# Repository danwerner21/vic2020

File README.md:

# Vic-2020
A Vic-20 clone created with [almost] all readily available parts

## Introduction
This project is an implementation of a VIC-20 (mostly) compatible computer. The project is built using a combination of 1980's era components (7400-series logic) and more modern components- such as a modern 6502 variant and 512 KiB SRAM and 512 KiB Flash ROMs. The only hard to find component is the MOS 6560 VIC video chip -- and it is my hope to follow up this project with a project to replace that chip with a FPGA replacement, providing the open source community a full path to re-creating the VIC-20 with all new components.

## Why?
Why would I do a replica of the VIC-20?   Well, like many others the VIC-20 was my first computer.  In 1981 I spent most of my (non-school) waking hours learning everything possible about this machine, and that launched me into a successful career in IT.   In the early 2000s I discovered the retro-computer scene and have spent many hours building and creating new retro computer designs following the work happening in such places as 6502.org and retrobrewcomputers.org.  So much so, that my boss has taken to giving me crap about spending my free time "Building VIC-20s" . . . .   It was earlier in 2020 when he had made one such comment that I realized that while I had constructed many vintage designs, I had never actually built a VIC-20.  I decided that I should correct that oversight as soon as possible -- and thus the VIC-2020 Fichter Edition (named after my boss) was born.

---

## What is included in this repo?
As of this time, the repo includes

1. The VIC-2020 Mainboard PCB Kicad design and Gerber files
2. The VIC-2020 Keyboard PCB Kicad design and Gerber files
3. OpenSCAD and STL files for a 3d printed case
4. Design Files for Max Keyboard Custom Printed Keycaps

---

## Known Bugs

* While the mainboard does have a S-VIDEO mod applied that should (in theory) provide S-VIDEO output, it does not work.   If anyone corrects this, please feel free to reach out and I will correct the schematics -- but for now, I would not populate the S-VIDEO connector, and always short the Chroma Disconnect jumper.
#### UPDATE
 Turns out the footprint for the SVIDEO connector in KiCad has the pins numbered incorrectly and that is the cause of the SVIDEO issue.   I have updated the PCB and Schematic to account for this, but have not tested the fix myself.  I am told that the SVIDEO out does work with a properly wired cable.

 note that the 1.1 version of the PCB still have the Chroma/Luma pins reversed on the video connector.  Seems that I made a patch to correct the pins and KiCAD also made a patch to correct the PCB layout of the connector, and thus reversed each other's work. . .  1.2 should be correct, but as always until it is tested, assume it needs patched.

---

## How is the VIC-2020 the same as a VIC-20?

The VIC-2020 should be mostly software compatible with the expanded and unexpanded Commodore VIC-20.   I have tested a variety of cartridges (commodore and third party) and have ran several homebrew and commercial disk based programs on the system with no issues.   Note that this does use a more modern variant of the 6502, so software relying on 6502 undocumented opcodes or bugs will not work properly.  The VIC-2020 has a commodore compatible IEC port that has been tested with a real 1571 and real 1541 and seems to work properly with one exception -- if the device holds the RESET line low the system will not function.   This can be observed if the VIC-2020 is connected to a powered off IED device -- the VIC will not function until the IEC device is powered on or unplugged from the VIC.

---

## How is the VIC-2020 different from a VIC-20?

Because the VIC-2020 is using more modern parts, it has ALOT of ram compared to the VIC-20.   The original VIC-20 shipped with 4k of ram . . .  the VIC-2020 has 256k.  This has some implications.   First, for compatibility there is a portion of the RAM that is just wasted. Of the 128k chip that is used for main memory, only 32k is accessible, the rest is hidden.  This is a design trade off that made the system less complex and ensured compatibility.   That said, small design changes were made to allow the 128k color ram to be totally usable by the system.  The first modification allowed all 8 bits of color ram to be used as storage for the system.  In the original VIC-20, color ram was only 4 bits wide, as the VIC chip only needs 4 bits to store color information.  In the VIC-2020 design all 8 bits are available to the CPU, even though only 4 bits are used by the VIC chip.  This should allow a programmer to store user information in the upper 4 bits of the color ram without affecting any other part of the system.   Also, the 6522 IO port that was dedicated to the user port on the VIC-20 has been repurposed as a "Page Register" (located at 0x9110 or 37136) on the VIC-2020 allowing 128 pages of color ram to be available for the VIC chip.  This should give the ability for some very interesting color effects to be produced on the VIC-2020, while still keeping the VIC mostly compatible.  This technique was demonstrated as early as 2010 in the sleepingelephant.com forums [here](http://sleepingelephant.com/ipw-web/bulletin/bb/viewtopic.php?t=4882).

### Power
Unlike the original, the VIC-2020 will run off of one regulated 5V 1.5A power supply.

### Ports
In order to simplify the VIC-2020s power requirements, the cassette and user ports were ommitted from the system.   It is possible to use the lines in the AUX connector (J11) and the IEC port to gain access to the cassette data lines if one wanted to use a cassette emulator.  The cartridge port is mostly compatible (assuming proper setting of SW3) with the omission of the RAM1,RAM2, & RAM3 lines.
Note that trimmer RV1 can be used to adjust video signal output strength.  If your particular TV appears either overdriven or too dim, adjust RV1 accordingly.   Variable Cap C2 can be used to adjust video signal phase -- adjust this trimmer if your VIC shows no color or the wrong colors.

### Ram Configuration
For simplicity sake, the VIC-2020 in even its lowest memory configuration has the VIC 3K memory expansion enabled at RAM1, RAM2, and RAM3, giving it 8K of base ram, 6.5k free for BASIC.   This configuration is totally compatible with most "unexpanded" VIC software, but is incompatible with any cartridge that includes the 3k RAM expansion option (such as the VIC Super Expander Cartridge).  The other RAM configuration options for BLK1, BLK2, BLK3, and BLK5 are DIP switch selectable allowing memory to be configured.   It is best to have each RAM block only assigned to either the Expansion Port (SW3) or the Internal RAM (SW1) but not both at the same time.  When in doubt set all of SW3 to "on" and all of SW1 to "off" and you should have a mostly compatible unexpanded VIC.  For a mostly compatible expanded VIC set BLK1,BLK2, BLK3 on SW1 to "on" and SW3 to "off".

### Character ROM Configuration
The 8K 2764 EPROM at U19 contains the character ROM image for the VIC-2020.  The VIC chip only needs 4K to store a complete set of character images, so jumper J3 is used to select one of two character sets that can be stored on the 2764.  If pins 1&2 are shorted on the jumper the first 4K of the chip is used (addresses 0x0000-0x0FFF) for the character patterns and if pins 2&3 are shorted the second 4K (addresses 0x1000-0x1FFF) are used.

### System ROM Configuration
On the VIC-2020 it is possible to use several different types of main ROM chips and have several ROM images burned at the same time -- all selected by jumpers J1 and J2.

Jumper Settings|Chip Used|Resulting eprom configuration
---------------|---------|-----------------------
J1 1&2, J2 1&2|27512         | BASIC image at 0x0000 through 0x1FFF KERNAL at 0x2000 through 0x3FFF
J1 1&2, J2 1&2|27256         | BASIC image at 0x0000 through 0x1FFF KERNAL at 0x2000 through 0x3FFF
J1 1&2, J2 1&2|27128         | BASIC image at 0x0000 through 0x1FFF KERNAL at 0x2000 through 0x3FFF
J1 1&2, J2 2&3|27512         | BASIC image at 0x4000 through 0x5FFF KERNAL at 0x6000 through 0x7FFF
J1 1&2, J2 2&3|27256         | BASIC image at 0x4000 through 0x5FFF KERNAL at 0x6000 through 0x7FFF
J1 1&2, J2 2&3|27128         | NOT VALID
J1 2&3, J2 1&2|27512         | BASIC image at 0x8000 through 0x9FFF KERNAL at 0xA000 through 0xBFFF
J1 2&3, J2 1&2|27256         | NOT VALID
J1 2&3, J2 1&2|27128         | NOT VALID
J1 2&3, J2 1&2|27512         | BASIC image at 0xC000 through 0xDFFF KERNAL at 0xE000 through 0xFFFF
J1 2&3, J2 1&2|27256         | NOT VALID
J1 2&3, J2 1&2|27128         | NOT VALID

---

## Bill Of Materials

### Mainboard

Part Number|Quantity|Name
-----------|--------|----
C35,C36	|2|	.001uf Capacitor
C7,C12-C34|	23|	.01uf Capacitor
C1,C6,C8,C10,C40|	5|	.1uf Capacitor
C37	|1|	.47uF Electrolytic Capacitor
C38	|1|	10uF Electrolytic Capacitor
C4	|1|	10uf Capacitor
C11	|1|	1uf Electrolytic Capacitor
C9	|1|	2.2uF Electrolytic Capacitor
C5	|1|	220pf Capacitor
C3	|1|	2pf Capacitor
C39	|1|	47uF Capacitor
C2	|1|	8-90pf  Variable Capacitor
FB1-FB9|	9|	Ferrite_Bead_Small
J1,J2,J3|	3|	Pin Header 1x03 2.54mm
J10	|1|	Barrel Jack
J11	|1|	Pin Header 2x8 2.54mm
J12	|1|	Card Edge Connector 2x22 (Mouser #:587-305-044-520-502)
J13	|1|	DIN 6 IEC connector (mouser#571-9-211509)
J14	|1|	DSUB 9 Male
J4,J9	|2|	Pin Header 1x2 2.54mm
J5	|1|	DIN-4 (mouser#571-5749181-1)
J6,J7	|2|	RCA Jack
J8	|1|	Pin Header 1x20
Q1	|1|	2sc1959
Q2	|1|	2SC1815
R36	|1|	75ohm Resistor 1/4w
R15	|1|	180ohm Resistor 1/4w
R16	|1|	240ohm Resistor 1/4w
R22	|1|	270ohm Resistor 1/4w
R2,R4,R24	|3|	330ohm Resistor 1/4w
R21	|1|	470ohm Resistor 1/4w
R17	|1|	510ohm Resistor 1/4w
R3,R5	|2|	560ohm Resistor 1/4w
R19	|1|	1.8Kohm Resistor 1/4w
R23	|1|	10Kohm Resistor 1/4w
R6	|1|	150Kohm Resistor 1/4w
R7,R11-R14,R18,R25-R35	|16|	1K ohm Resistor 1/4w
R8-R10	|3|	2.2Kohm Resistor 1/4w
R20	|1|	2.7Kohm Resistor 1/4w
R1	|1|	220kohm Resistor 1/4w
RV1	|1|	1Kohm Variable Resistor (Mouser# 531-PT10LV112A22PMS)
SW1,SW3	|2|	DIP Switch 4 pos
U19	|1|	2764
U20	|1|	6560 (MOS, VIC-20 pull or E-Bay)
U1	|1|	7402
U4	|1|	7406
U13	|1|	27512
U24	|1|	74ALS32
U8	|1|	74LS00
U11	|1|	74LS02
U9	|1|	74LS04
U5,U10	|2|	74LS133
U2,U6	|2|	74LS138
U14,U15,U16,U18,U23	|5|	74LS245
U12,U17	|2|	AS6C1008-55PCN
U3	|1|	LM555
U7	|1|	W65C02SxP
U21,U22	|2|	W65C22NxP
Y1	|1|	Crystal 14.31818Mhz

### Keyboard

Quantity|Name
--------|----
65|Cherry MX Switch | (Example Mouser 540-MX1A-11NW)
4|Switch Leveling Kit| Mouser 540-G99-0226 Note: Use one of 540-G99-0742 to build a through hole leveling kit for the spacebar
1|Pin Header 1x20
1|Pin Header 1x2 or LED
1|330 Ohm Resistor
1| Keycap set (See Max Keyboard Template to order custom keycaps)
1| 1x20 Female to Female dupont connector ribbon cable to connect keyboard to mainboard

### Case

The case for the Vic-2020 was created using openSCAD and was printed on the AnyCubic Chiron large format printer.   The OpenSCAD source files and the STL files are included in the archive.  The case is designed to allow you to install a power led in the upper left corner.   The opening is intended for two rectangular LEDs glued as shown here:

It is also necessary to install a stabilizer on one corner of the keyboard to ensure that the keyboard PCB does not flex while typing.  This is how I did it:

When complete, the interior of the 3d printed case will look like this:

### Builder Comments

Below is a couple of observations from builders that might be useful in your build.  I have not tested any of these suggestions, just passing on collective wisdom :)

* One bulder commented that he needed to replace U9 (74LS04->74F04) and U11 (74LS02->74F02) with F series logic in order to get clean RAM access.   I have not had a need to do this on any of my builds, but timing is very tight on this board, and it is always possible that these substitutions would help clear up issues.  This same builder needed to use a Rockwell 65C02 in place of the WDC 65C02 to get a stable build.

* Another builder noted that is is important to use a 2764 EPROM for the character ROM.   A 27C64 EPROM caused graphical glitching when used.

* It was recently reported that at least one builder has had success using a 6561 PAL VIC chip to replace the 6560 NTSC VIC chip.  It is also necessary to replce the 14.31818Mhz crystal with a 4.433618 MHz crystal in a PAL system.

### Questions?

If there are any questions, I can be reached at vic2020Dan at gmail dot com.

---

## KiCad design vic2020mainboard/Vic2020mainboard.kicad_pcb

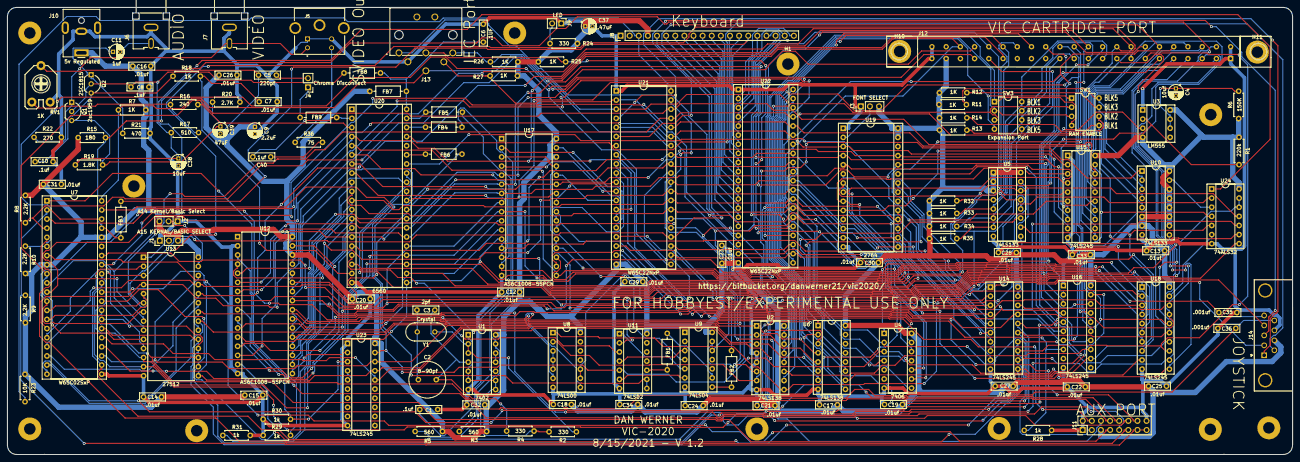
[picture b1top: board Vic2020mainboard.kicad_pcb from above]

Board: 2 copper layers, 357.8 x 124.5 mm, 142 parts (0 on the bottom side), 186 nets.

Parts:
C1, C10, C40: .1uf; C_Rect_L7.0mm_W2.0mm_P5.00mm
C2: 8-90pf; C_Radial_D10.0mm_H12.5mm_P5.00mm
C3: 2pf; C_Rect_L7.0mm_W2.0mm_P5.00mm
C4: 10uf; CP_Radial_D4.0mm_P2.00mm
C5: 220pf; C_Rect_L7.0mm_W2.0mm_P5.00mm
C6: .1UF; C_Rect_L7.0mm_W2.0mm_P5.00mm
C7, C12, C13, C14, C15, C16, C17, C18, C19, C20, C21, C22, C23, C24, C25, C26, C27, C28, C29, C30, C31, C32, C33, C34: .01uf; C_Rect_L7.0mm_W2.0mm_P5.00mm
C8: .1uF; C_Rect_L7.0mm_W2.0mm_P5.00mm
C9: 2.2uF; CP_Radial_D4.0mm_P2.00mm
C11: 1uf; CP_Radial_D4.0mm_P2.00mm
C35, C36: .001uf; C_Rect_L7.0mm_W2.0mm_P5.00mm
C37: .47uF; CP_Radial_D4.0mm_P2.00mm
C38: 10uF; CP_Radial_D4.0mm_P2.00mm
C39: 47uF; CP_Radial_D4.0mm_P2.00mm
FB1, FB2, FB3, FB4, FB5, FB6, FB8, FB9: Ferrite_Bead_Small; L_Axial_L6.6mm_D2.7mm_P10.16mm_Horizontal_Vishay_IM-2
FB7: L_Axial_L6.6mm_D2.7mm_P10.16mm_Horizontal_Vishay_IM-2
H1, H2, H3, H4, H5, H6, H7, H8, H10, H11, H12, H13, H14: MountingHole; MountingHole_3.2mm_M3_Pad
J1: A15 KERNAL/BASIC SELECT; PinHeader_1x03_P2.54mm_Vertical
J2: A14 Kernel/Basic Select; PinHeader_1x03_P2.54mm_Vertical
J3: FONT SELECT; PinHeader_1x03_P2.54mm_Vertical
J4: Chroma Disconnect; PinHeader_1x02_P2.54mm_Vertical
J5: SVIDEO Out; DIN-4TE_5749181-1
J6: Audio Out; CUI_RCJ-041-reversepins
J7: Video Out; CUI_RCJ-041-reversepins
J8: Keyboard; PinHeader_1x20_P2.54mm_Vertical
J9: LED; PinHeader_1x02_P2.54mm_Vertical
J10: 5v Regulated; BarrelJack_CUI_PJ-063AH_Horizontal
J11: Conn_02x08_Odd_Even; PinHeader_2x08_P2.54mm_Vertical
J12: Conn_02x22_Row_Letter_First; vic20cartridge1
J13: IEC Port; din6
J14: Joystick 1; DSUB-9_Male_Horizontal_P2.77x2.84mm_EdgePinOffset4.94mm_Hou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
Q1: 2sc1959; TO-92_Inline_Wide
Q2: 2SC1815; TO-92_Inline_Wide
R1: 220k; R_Axial_DIN0207_L6.3mm_D2.5mm_P7.62mm_Horizontal
R2, R4, R24: 330; R_Axial_DIN0207_L6.3mm_D2.5mm_P7.62mm_Horizontal
R3, R5: 560; R_Axial_DIN0207_L6.3mm_D2.5mm_P7.62mm_Horizontal
R6: 150K; R_Axial_DIN0207_L6.3mm_D2.5mm_P7.62mm_Horizontal
R7, R11, R12, R13, R14, R18, R25, R26, R27, R32, R33, R34, R35: 1K; R_Axial_DIN0207_L6.3mm_D2.5mm_P7.62mm_Horizontal
R8, R9, R10: 2.2K; R_Axial_DIN0207_L6.3mm_D2.5mm_P7.62mm_Horizontal
R15: 180; R_Axial_DIN0207_L6.3mm_D2.5mm_P7.62mm_Horizontal
R16: 240; R_Axial_DIN0207_L6.3mm_D2.5mm_P7.62mm_Horizontal
R17: 510; R_Axial_DIN0207_L6.3mm_D2.5mm_P7.62mm_Horizontal
R19: 1.8K; R_Axial_DIN0207_L6.3mm_D2.5mm_P7.62mm_Horizontal
R20: 2.7K; R_Axial_DIN0207_L6.3mm_D2.5mm_P7.62mm_Horizontal
R21: 470; R_Axial_DIN0207_L6.3mm_D2.5mm_P7.62mm_Horizontal
R22: 270; R_Axial_DIN0207_L6.3mm_D2.5mm_P7.62mm_Horizontal
R23: 10K; R_Axial_DIN0207_L6.3mm_D2.5mm_P7.62mm_Horizontal
R28, R29, R30, R31: 1k; R_Axial_DIN0207_L6.3mm_D2.5mm_P7.62mm_Horizontal
R36: 75; R_Axial_DIN0207_L6.3mm_D2.5mm_P7.62mm_Horizontal
RV1: 1K; Potentiometer_Trimmer_2x4.kicad_mod
SW1: RAM ENABLE; DIP-8_W7.62mm
SW3: Expansion Port; DIP-8_W7.62mm
U1: 7402; DIP-14_W7.62mm_Socket
U2, U6: 74LS138; DIP-16_W7.62mm_Socket
U3: LM555; DIP-8_W7.62mm_Socket
U4: 7406; DIP-14_W7.62mm_Socket
U5, U10: 74LS133; DIP-16_W7.62mm_Socket
U7: W65C02SxP; DIP-40_W15.24mm_Socket
U8: 74LS00; DIP-14_W7.62mm_Socket
U9: 74LS04; DIP-14_W7.62mm_Socket
U11: 74LS02; DIP-14_W7.62mm_Socket
U12, U17: AS6C1008-55PCN; DIP-32_W15.24mm
U13: 27512; DIP-28_W15.24mm
U14, U15, U16, U18, U23: 74LS245; DIP-20_W7.62mm_Socket
U19: 2764; DIP-28_W15.24mm_Socket
U20: 6560; DIP-40_W15.24mm_Socket
U21, U22: W65C22NxP; DIP-40_W15.24mm_Socket
U24: 74ALS32; DIP-14_W7.62mm_Socket
Y1: Crystal; Crystal_HC18-U_Vertical

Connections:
A0: J12.b2, U7.9, U13.10, U15.18, U21.38, U22.38
A1: J12.b3, U7.10, U13.9, U15.17, U21.37, U22.37
A2: J12.b4, U7.11, U13.8, U15.16, U21.36, U22.36
A3: J12.b5, U7.12, U13.7, U15.15, U21.35, U22.35
A4: J12.b6, U7.13, U13.6, U15.14, U21.24
A5: J12.b7, U7.14, U13.5, U15.13, U22.24
A6: J12.b8, U7.15, U13.4, U15.12
A7: J12.b9, U7.16, U13.3, U15.11
A8: J12.b10, U7.17, U13.25, U16.18
A9: J12.b11, U7.18, U13.24, U16.17
A10: J12.b12, U6.1, U7.19, U13.21, U16.16
A11: J12.b13, U6.2, U7.20, U13.23, U16.15
A12: J12.b14, U6.3, U7.22, U13.2, U16.14
A13: J12.b15, U2.1, U6.4, U7.23, U13.26, U23.18
A14: U2.2, U6.5, U7.24, U23.17
A15: U2.3, U6.6, U7.25, U23.16
AUDIOOUT: C11.2, J6.1
BD0: U12.13, U14.2, U19.11, U20.16, U21.33, U22.33
BD1: U12.14, U14.3, U19.12, U20.15, U21.32, U22.32
BD2: U12.15, U14.4, U19.13, U20.14, U21.31, U22.31
BD3: U12.17, U14.5, U19.15, U20.13, U21.30, U22.30
BD4: U12.18, U14.6, U19.16, U20.12, U21.29, U22.29
BD5: U12.19, U14.7, U19.17, U20.11, U21.28, U22.28
BD6: U12.20, U14.8, U19.18, U20.10, U21.27, U22.27
BD7: U12.21, U14.9, U19.19, U20.9, U21.26, U22.26
BLK0: U2.15, U10.1
BLK1: SW1.4, SW3.1, U2.14
BLK2: SW1.3, SW3.2, U2.13
BLK3: SW1.2, SW3.3, U2.12
BLK4: U2.11, U16.13
BLK5: SW1.1, SW3.4, U2.10
BLK6: U2.9, U5.15, U8.1
BLK7: U2.7, U5.11, U8.2
CBLK1: J12.a10, R32.2, SW3.8, U5.4
CBLK2: J12.a11, R33.2, SW3.7, U5.5
CBLK3: J12.a12, R34.2, SW3.6, U5.6
CBLK5: J12.a13, R35.2, SW3.5, U5.7
CENB: R28.2, U16.8, U17.22, U17.24
CHROMA: C40.2, FB9.2, U20.2
CHRROM: U9.12, U24.2
COL0: J8.12, U22.10
COL1: J8.11, U22.11
COL2: J8.10, U22.12
COL3: J8.9, U22.13
COL4: J8.8, U22.14
COL5: J8.7, U22.15
COL6: J8.6, U22.16
COL7: J8.5, J14.4, U22.17
COLOR: U5.10, U6.10, U16.12, U24.5
CPU02: U7.39, U11.8, U11.9
CSRAM: U8.8, U12.22, U12.24
CSROM: U8.6, U13.20, U13.22
D0: J12.a2, U7.33, U13.11, U14.18, U18.18
D1: J12.a3, U7.32, U13.12, U14.17, U18.17
D2: J12.a4, U7.31, U13.13, U14.16, U18.16
D3: J12.a5, U7.30, U13.15, U14.15, U18.15
D4: J12.a6, U7.29, U13.16, U14.14, U18.14
D5: J12.a7, U7.28, U13.17, U14.13, U18.13
D6: J12.a8, U7.27, U13.18, U14.12, U18.12
D7: J12.a9, U7.26, U13.19, U14.11, U18.11
DATAE: U5.9, U14.19
E: FB6.2, U4.3, U11.5, U15.19, U16.19, U23.19, U24.4
GND: C1.2, C4.2, C6.2, C7.2, C8.2, C9.2, C10.2, C12.2, C13.2, C14.2, C15.2, C16.2, C17.2, C18.2, C19.2, C20.2, C21.2, C22.2, C23.2, C24.2, C25.2, C26.2, C27.2, C28.2, C29.2, C30.2, C31.2, C32.2, C33.2, C34.2, C35.2, C36.2, C37.2, C38.2, J1.1, J2.1, J3.1, J5.1, J5.2, J6.2, J7.2, J8.1, J9.1, J10.2, J11.1, J11.2, J11.16, J12.a1, J12.a22, J12.b1, J12.b22, J13.2, J14.8, R20.2, R21.2, R22.2, R28.1, R29.1, R30.1, R31.1, RV1.3, U1.7, U2.4, U2.5, U2.8, U3.1, U4.7, U5.8, U6.8, U7.21, U8.7, U9.7, U10.8, U11.7, U12.2, U12.16, U13.14, U14.10, U15.1, U15.10, U16.1, U16.10, U17.16, U18.10, U19.1, U19.14, U20.20, U21.1, U22.1, U23.1, U23.10, U24.7
IO0: U6.11, U21.23, U22.23
IO2: J12.b16, U5.12, U6.9
IO3: J12.b17, U5.13, U6.7
IRQ: J12.a19, R8.1, U7.4, U22.21
JOY0: J14.1, U21.4
JOY1: J14.2, U21.5
JOY2: J14.3, U21.6
LPEN: J14.6, U20.37, U21.7
LUMA: R16.2, U20.3
MA13: R29.2, U12.28, U23.2
MA14: R30.2, U12.3, U23.3
MA15: R31.2, U12.31, U23.4
ML: J11.11, U7.5
NMI: J12.b19, R10.1, U7.6, U21.21
unnamed: C1.1, R1.2, U3.2
unnamed: C2.1, C3.2, Y1.2
unnamed: C2.2, C3.1, R4.1, U1.4, U1.11, U1.12
unnamed: C4.1, R6.2, U3.6, U3.7
unnamed: C5.2, J4.2
unnamed: C6.1, FB7.2, FB8.2, U20.40
unnamed: C10.1, Q2.3, R18.1
unnamed: C11.1, Q2.1, R21.1
unnamed: C8.1, C38.1, FB8.1, Q1.2, Q2.2, R17.1, R19.1
unnamed: C39.1, Q1.3, R19.2, R20.1
unnamed: C5.1, C39.2, RV1.2
unnamed: C40.1, R36.2
unnamed: FB1.1, U9.9
unnamed: FB1.2, U11.10
unnamed: FB2.1, U24.12, U24.13
unnamed: FB2.2, U9.8
unnamed: FB3.2, U4.4
unnamed: FB4.1, U20.38
unnamed: FB5.1, U20.39
unnamed: FB6.1, U20.35
unnamed: FB9.1, J4.1
unnamed: J1.2, U13.1
unnamed: J2.2, U13.27
unnamed: J3.2, U19.2
unnamed: J9.2, R24.2
unnamed: J13.3, R25.2, U4.12
unnamed: R2.1, R4.2, U1.1, U1.5, U1.6, U1.8, U1.9
unnamed: R2.2, U1.2, U1.3, Y1.1
unnamed: R11.1, SW1.8, U10.2
unnamed: R12.2, SW1.7, U10.3
unnamed: R13.2, SW1.6, U10.4
unnamed: R14.2, SW1.5, U10.5
unnamed: R16.1, R17.2, RV1.1
unnamed: U3.3, U4.1
unnamed: U8.3, U8.4, U8.5
unnamed: U8.9, U8.10, U10.9
unnamed: U9.5, U11.1
unnamed: U9.3, U11.4
unnamed: U9.6, U11.6
unnamed: U18.19, U24.6
unnamed: U9.13, U24.8
O1: U7.3, U11.3
PA6: J11.4, U21.8
PB0: U17.23, U21.10
PB1: U17.25, U21.11
PB2: U17.4, U21.12
PB3: U17.28, U21.13
PB4: U17.3, U21.14
PB5: U17.31, U21.15
PB6: U17.2, U21.16
PB7: J11.6, U21.17
POTX: C36.1, J14.9, U20.17
POTY: C35.1, J14.5, U20.18
RDY: J11.13, J11.15, R9.1, U7.2, U7.38
RESET: J11.3, J12.b20, J13.6, R7.1, U4.2, U7.40, U21.34, U22.34
RESTORE: J8.3, R23.2, U21.40
ROW0: J8.20, U22.2
ROW1: J8.19, U22.3
ROW2: J8.18, U22.4
ROW3: J8.17, U22.5
ROW4: J8.16, U22.6
ROW5: J8.15, U22.7
ROW6: J8.14, U22.8
ROW7: J8.13, U22.9
RW: J12.a18, U7.34, U11.2, U14.1, U18.1, U21.22, U22.22
SERATNOUT: U4.13, U21.9
SERCLKIN: J13.4, R27.2, U4.10, U21.2
SERCLKOUT: U4.11, U22.39
SERDATAIN: J13.5, R26.2, U4.8, U21.3
SERDATAOUT: U4.9, U22.19
SERSRQ: J13.1, U22.18
SO0: FB3.1, R15.2, U7.37, U24.1
SO2: J12.b18, U2.6, U5.14, U21.25, U22.25, U24.11
SVIDC: J5.4, R36.1
SYNC: J11.7, U7.7
VA0: U12.12, U15.2, U17.12, U19.10, U20.21
VA1: U12.11, U15.3, U17.11, U19.9, U20.22
VA2: U12.10, U15.4, U17.10, U19.8, U20.23
VA3: U12.9, U15.5, U17.9, U19.7, U20.24
VA4: U12.8, U15.6, U17.8, U19.6, U20.25
VA5: U12.7, U15.7, U17.7, U19.5, U20.26
VA6: U12.6, U15.8, U17.6, U19.4, U20.27
VA7: U12.5, U15.9, U17.5, U19.3, U20.28
VA8: U12.27, U16.2, U17.27, U19.25, U20.29
VA9: U12.26, U16.3, U17.26, U19.24, U20.30
VA10: U12.23, U16.4, U19.21, U20.31
VA11: U12.25, U16.5, U19.23, U20.32
VA12: U12.4, U16.6, U19.22, U20.33, U24.10
VA13: U16.7, U19.20, U20.34, U24.9
VCC: C9.1, C12.1, C13.1, C14.1, C15.1, C16.1, C17.1, C18.1, C19.1, C20.1, C21.1, C22.1, C23.1, C24.1, C25.1, C26.1, C27.1, C28.1, C29.1, C30.1, C31.1, C32.1, C33.1, C34.1, C37.1, FB7.1, J1.3, J2.3, J3.3, J8.4, J10.1, J11.5, J12.a21, J14.7, R1.1, R3.2, R5.2, R6.1, R7.2, R8.2, R9.2, R10.2, R11.2, R12.1, R13.1, R14.1, R15.1, R23.1, R24.1, R25.1, R26.1, R27.1, R32.1, R33.1, R34.1, R35.1, U1.14, U2.16, U3.4, U3.8, U4.14, U5.1, U5.2, U5.3, U5.16, U6.16, U7.8, U7.36, U8.14, U9.14, U10.6, U10.7, U10.10, U10.11, U10.12, U10.13, U10.14, U10.16, U11.14, U12.30, U12.32, U13.28, U14.20, U15.20, U16.20, U17.30, U17.32, U18.20, U19.27, U19.28, U21.20, U22.20, U23.20, U24.14
VD8: U17.13, U18.2, U20.8
VD9: U17.14, U18.3, U20.7
VD10: U17.15, U18.4, U20.6
VD11: U17.17, U18.5, U20.5
VD12: U17.18, U18.6
VD13: U17.19, U18.7
VD14: U17.20, U18.8
VD15: U17.21, U18.9
VIA1CA1: J11.8, U22.40
VIA1CA2: J11.10, U21.39
VIA1CB1: J11.12, U21.18
VIA1CB2: J11.14, U21.19
VICAUDIO: C7.1, R18.2, U20.19
VICO1: FB5.2, R3.1, U1.10
VICO2: FB4.2, R5.1, U1.13
VIDEOOUT: J5.3, J7.1, Q1.1, R22.1
VIDRAM: U10.15, U24.3
VP: J11.9, U7.1
VRW: J12.a17, U9.4, U12.29, U17.29, U20.4

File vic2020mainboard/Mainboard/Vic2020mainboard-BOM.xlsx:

Reference | Qty | Value | Source
C35,C36 | 2 | .001uf Capacitor | mouser# 594-S102M33Z5UR63L6R
C7,C12-C34 | 23 | .01uf Capacitor | Capacitor_THT:C_Rect_L7.0mm_W2.0mm_P5.00mm
C1,C6,C8,C10,C40 | 5 | .1uf Capacitor | Capacitor_THT:C_Rect_L7.0mm_W2.0mm_P5.00mm
C37 | 1 | .47uF Electrolytic Capacitor | Capacitor_THT:CP_Radial_D4.0mm_P2.00mm
C38 | 1 | 10uF Electrolytic Capacitor | Capacitor_THT:CP_Radial_D4.0mm_P2.00mm
C4 | 1 | 10uf Capacitor | Capacitor_THT:C_Rect_L7.0mm_W2.0mm_P5.00mm
C11 | 1 | 1uf Electrolytic Capacitor | Capacitor_THT:CP_Radial_D4.0mm_P2.00mm
C9 | 1 | 2.2uF Electrolytic Capacitor | Capacitor_THT:CP_Radial_D4.0mm_P2.00mm
C5 | 1 | 220pf Capacitor | Capacitor_THT:C_Rect_L7.0mm_W2.0mm_P5.00mm
C3 | 1 | 2pf Capacitor | Capacitor_THT:C_Rect_L7.0mm_W2.0mm_P5.00mm
C39 | 1 | 47uF Capacitor | Capacitor_THT:CP_Radial_D4.0mm_P2.00mm
C2 | 1 | 8-90pf Variable Capacitor | Capacitor_THT:C_Radial_D10.0mm_H12.5mm_P5.00mm
FB1-FB9 | 9 | Ferrite_Bead_Small | Inductor_THT:L_Axial_L6.6mm_D2.7mm_P10.16mm_Horizontal_Vishay_IM-2
J1,J2,J3 | 3 | Pin Header 1x03 2.54mm | Connector_PinHeader_2.54mm:PinHeader_1x03_P2.54mm_Vertical
J10 | 1 | Barrel Jack | Connector_BarrelJack:BarrelJack_CUI_PJ-063AH_Horizontal
J11 | 1 | Pin Header 2x8 2.54mm | Connector_PinHeader_2.54mm:PinHeader_2x08_P2.54mm_Vertical
J12 | 1 | Card Edge Connector 2x22 (Mouser #:587-305-044-520-502) | Mouser #:587-305-044-520-502
J13 | 1 | DIN 6 IEC connector (mouser#571-9-211509) | 587-305-044-520-502
J14 | 1 | DSUB 9 Male | Connector_Dsub:DSUB-9_Male_Horizontal_P2.77x2.84mm_EdgePinOffset4.94mm_Housed_M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
J4,J9 | 2 | Pin Header 1x0 2.54mm | Connector_PinHeader_2.54mm:PinHeader_1x02_P2.54mm_Vertical
J5 | 1 | DIN-4 (mouser#571-5749181-1) | Connector:DIN-4TE_5749181-1
J6,J7 | 2 | RCA Jack | RCA:CUI_RCJ-041-reversepins
J8 | 1 | Pin Header 1x20 | Connector_PinHeader_2.54mm:PinHeader_1x20_P2.54mm_Vertical
Q1 | 1 | 2sc1959 | Package_TO_SOT_THT:TO-92_Inline_Wide
Q2 | 1 | 2SC1815 | Package_TO_SOT_THT:TO-92_Inline_Wide
R36 | 1 | 75ohm Resistor 1/4w | Resistor_THT:R_Axial_DIN0207_L6.3mm_D2.5mm_P7.62mm_Horizontal
R15 | 1 | 180ohm Resistor 1/4w | Resistor_THT:R_Axial_DIN0207_L6.3mm_D2.5mm_P7.62mm_Horizontal
R16 | 1 | 240ohm Resistor 1/4w | Resistor_THT:R_Axial_DIN0207_L6.3mm_D2.5mm_P7.62mm_Horizontal
R22 | 1 | 270ohm Resistor 1/4w | Resistor_THT:R_Axial_DIN0207_L6.3mm_D2.5mm_P7.62mm_Horizontal
R2,R4,R24 | 3 | 330ohm Resistor 1/4w | Resistor_THT:R_Axial_DIN0207_L6.3mm_D2.5mm_P7.62mm_Horizontal
R21 | 1 | 470ohm Resistor 1/4w | Resistor_THT:R_Axial_DIN0207_L6.3mm_D2.5mm_P7.62mm_Horizontal
R17 | 1 | 510ohm Resistor 1/4w | Resistor_THT:R_Axial_DIN0207_L6.3mm_D2.5mm_P7.62mm_Horizontal
R3,R5 | 2 | 560ohm Resistor 1/4w | Resistor_THT:R_Axial_DIN0207_L6.3mm_D2.5mm_P7.62mm_Horizontal
R19 | 1 | 1.8Kohm Resistor 1/4w | Resistor_THT:R_Axial_DIN0207_L6.3mm_D2.5mm_P7.62mm_Horizontal
R23 | 1 | 10Kohm Resistor 1/4w | Resistor_THT:R_Axial_DIN0207_L6.3mm_D2.5mm_P7.62mm_Horizontal
R6 | 1 | 150Kohm Resistor 1/4w | Resistor_THT:R_Axial_DIN0207_L6.3mm_D2.5mm_P7.62mm_Horizontal
R7,R11-R14,R18,R25-R35 | 16 | 1K ohm Resistor 1/4w | Resistor_THT:R_Axial_DIN0207_L6.3mm_D2.5mm_P7.62mm_Horizontal
R8-R10 | 3 | 2.2Kohm Resistor 1/4w | Resistor_THT:R_Axial_DIN0207_L6.3mm_D2.5mm_P7.62mm_Horizontal
R20 | 1 | 2.7Kohm Resistor 1/4w | Resistor_THT:R_Axial_DIN0207_L6.3mm_D2.5mm_P7.62mm_Horizontal
R1 | 1 | 220kohm Resistor 1/4w | Resistor_THT:R_Axial_DIN0207_L6.3mm_D2.5mm_P7.62mm_Horizontal
RV1 | 1 | 1Kohm Variable Resistor (Mouser# 531-PT10LV112A22PMS) | Varistor:Potentiometer_Trimmer_2x4.kicad_mod
SW1,SW3 | 2 | DIP Switch 4 pos | Package_DIP:DIP-8_W7.62mm
U19 | 1 | 2764 | Package_DIP:DIP-28_W15.24mm_Socket
U20 | 1 | 6560 (MOS, VIC-20 pull or E-Bay) | Package_DIP:DIP-40_W15.24mm_Socket
U1 | 1 | 7402 | Package_DIP:DIP-14_W7.62mm_Socket
U4 | 1 | 7406 | Package_DIP:DIP-14_W7.62mm_Socket
U13 | 1 | 27512 | Package_DIP:DIP-28_W15.24mm
U24 | 1 | 74ALS32 | Package_DIP:DIP-14_W7.62mm_Socket
U8 | 1 | 74LS00 | Package_DIP:DIP-14_W7.62mm_Socket
U11 | 1 | 74LS02 | Package_DIP:DIP-14_W7.62mm_Socket
U9 | 1 | 74LS04 | Package_DIP:DIP-14_W7.62mm_Socket
U5,U10 | 2 | 74LS133 | Package_DIP:DIP-16_W7.62mm_Socket
U2,U6 | 2 | 74LS138 | Package_DIP:DIP-16_W7.62mm_Socket
U14,U15,U16,U18,U23 | 5 | 74LS245 | Package_DIP:DIP-20_W7.62mm_Socket
U12,U17 | 2 | AS6C1008-55PCN | Package_DIP:DIP-32_W15.24mm
U3 | 1 | LM555 | Package_DIP:DIP-8_W7.62mm_Socket
U7 | 1 | W65C02SxP | Package_DIP:DIP-40_W15.24mm_Socket
U21,U22 | 2 | W65C22NxP | Package_DIP:DIP-40_W15.24mm_Socket
Y1 | 1 | Crystal 14.31818Mhz | Crystal:Crystal_HC18-U_Vertical

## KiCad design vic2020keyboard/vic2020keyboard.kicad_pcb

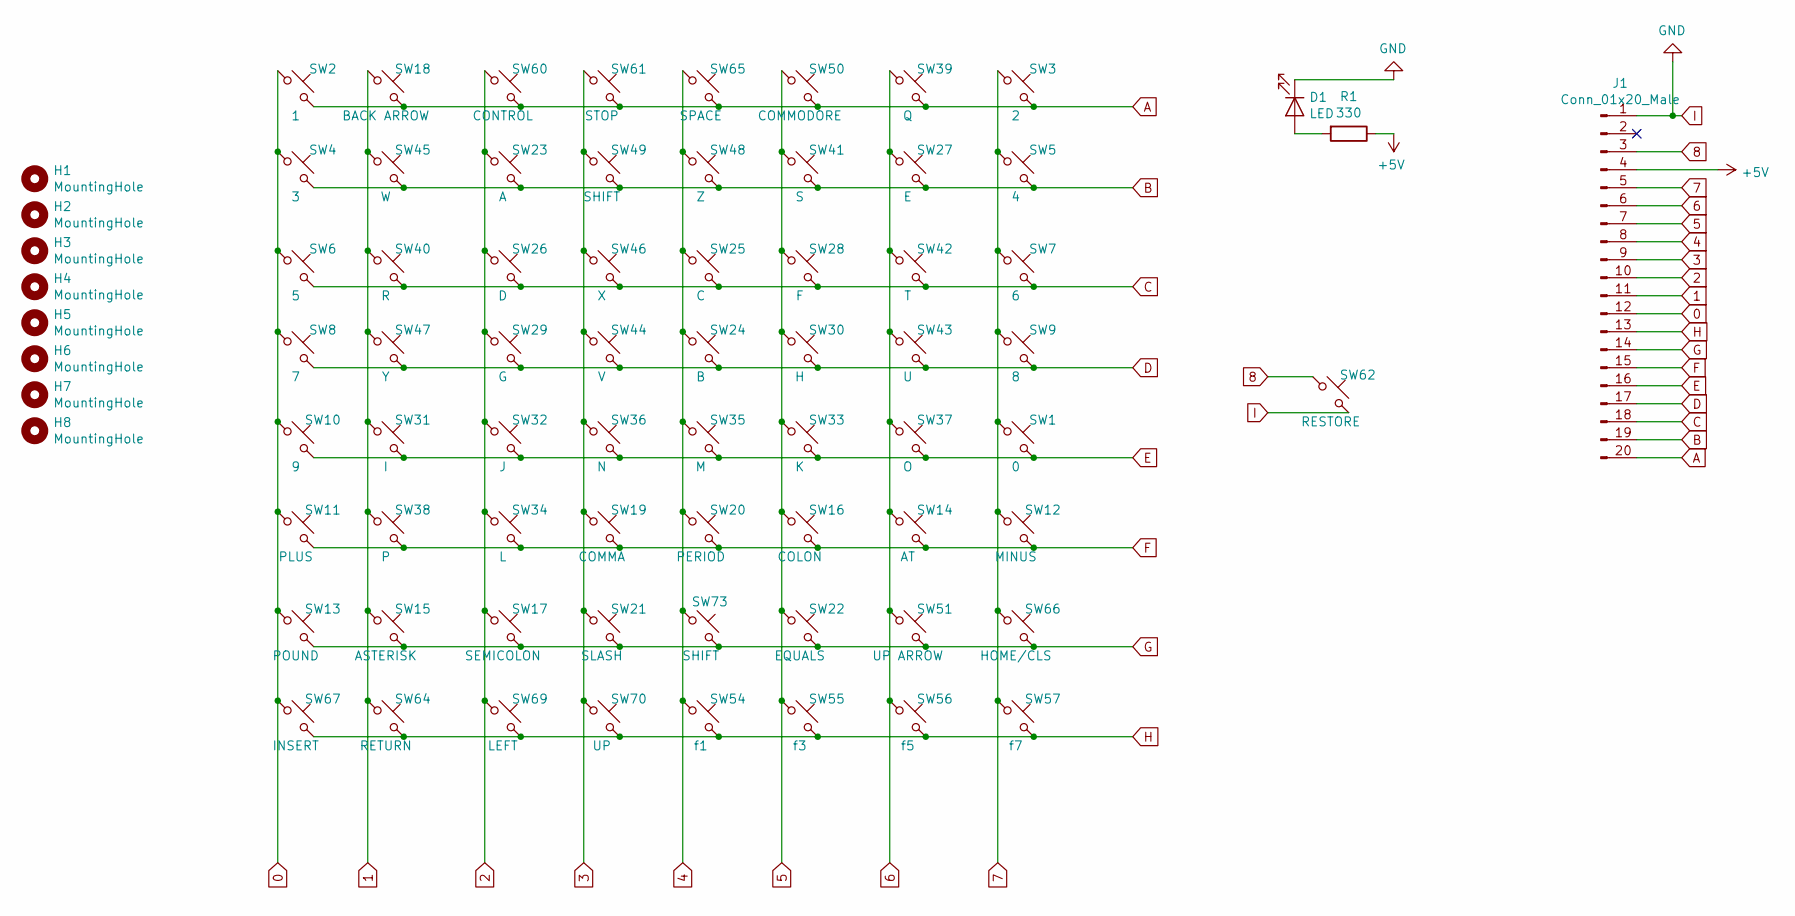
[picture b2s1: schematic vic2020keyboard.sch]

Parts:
D1: LED; LED_D5.0mm
H1, H2, H3, H4, H5, H6, H7, H8: MountingHole; MountingHole_3.2mm_M3_Pad
J1: Conn_01x20_Male; PinHeader_1x20_P2.54mm_Vertical
R1: 330; R_Axial_DIN0414_L11.9mm_D4.5mm_P7.62mm_Vertical
SW1: 0; CHERRY_PCB_100H
SW2: 1; CHERRY_PCB_100H
SW3: 2; CHERRY_PCB_100H
SW4: 3; CHERRY_PCB_100H
SW5: 4; CHERRY_PCB_100H
SW6: 5; CHERRY_PCB_100H
SW7: 6; CHERRY_PCB_100H
SW8: 7; CHERRY_PCB_100H
SW9: 8; CHERRY_PCB_100H
SW10: 9; CHERRY_PCB_100H
SW11: PLUS; CHERRY_PCB_100H
SW12: MINUS; CHERRY_PCB_100H
SW13: POUND; SW_Cherry_MX_1.00u_PCB
SW14: AT; CHERRY_PCB_100H
SW15: ASTERISK; CHERRY_PCB_100H
SW16: COLON; CHERRY_PCB_100H
SW17: SEMICOLON; CHERRY_PCB_100H
SW18: BACK ARROW; CHERRY_PCB_100H
SW19: COMMA; CHERRY_PCB_100H
SW20: PERIOD; CHERRY_PCB_100H
SW21: SLASH; CHERRY_PCB_100H
SW22: EQUALS; SW_Cherry_MX_1.00u_PCB
SW23: A; CHERRY_PCB_100H
SW24: B; CHERRY_PCB_100H
SW25: C; CHERRY_PCB_100H
SW26: D; CHERRY_PCB_100H
SW27: E; CHERRY_PCB_100H
SW28: F; CHERRY_PCB_100H
SW29: G; CHERRY_PCB_100H
SW30: H; CHERRY_PCB_100H
SW31: I; CHERRY_PCB_100H
SW32: J; CHERRY_PCB_100H
SW33: K; CHERRY_PCB_100H
SW34: L; CHERRY_PCB_100H
SW35: M; CHERRY_PCB_100H
SW36: N; CHERRY_PCB_100H
SW37: O; CHERRY_PCB_100H
SW38: P; CHERRY_PCB_100H
SW39: Q; CHERRY_PCB_100H
SW40: R; CHERRY_PCB_100H
SW41: S; CHERRY_PCB_100H
SW42: T; CHERRY_PCB_100H
SW43: U; CHERRY_PCB_100H
SW44: V; CHERRY_PCB_100H
SW45: W; CHERRY_PCB_100H
SW46: X; CHERRY_PCB_100H
SW47: Y; CHERRY_PCB_100H
SW48: Z; CHERRY_PCB_100H
SW49: SHIFT; CHERRY_PCB_225H
SW50: COMMODORE; CHERRY_PCB_125H
SW51: UP ARROW; SW_Cherry_MX_1.00u_PCB
SW54: f1; CHERRY_PCB_100H
SW55: f3; CHERRY_PCB_100H
SW56: f5; CHERRY_PCB_100H
SW57: f7; CHERRY_PCB_100H
SW60: CONTROL; SW_Cherry_MX_1.50u_PCB
SW61: STOP; SW_Cherry_MX_1.75u_PCB
SW62: RESTORE; SW_Cherry_MX_1.50u_PCB
SW64: RETURN; CHERRY_PCB_225H
SW65: SPACE; CHERRY_PCB_625H
SW66: HOME/CLS; CHERRY_PCB_100H
SW67: INSERT; CHERRY_PCB_100H
SW69: LEFT; CHERRY_PCB_100H
SW70: UP; CHERRY_PCB_100H
SW73: SHIFT; CHERRY_PCB_275H

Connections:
0: J1.12, SW2.1, SW4.1, SW6.1, SW8.1, SW10.1, SW11.1, SW13.1, SW67.1
1: J1.11, SW15.1, SW18.1, SW31.1, SW38.1, SW40.1, SW45.1, SW47.1, SW64.1
2: J1.10, SW17.1, SW23.1, SW26.1, SW29.1, SW32.1, SW34.1, SW60.1, SW69.1
3: J1.9, SW19.1, SW21.1, SW36.1, SW44.1, SW46.1, SW49.1, SW61.1, SW70.1
4: J1.8, SW20.1, SW24.1, SW25.1, SW35.1, SW48.1, SW54.1, SW65.1, SW73.1
5: J1.7, SW16.1, SW22.1, SW28.1, SW30.1, SW33.1, SW41.1, SW50.1, SW55.1
6: J1.6, SW14.1, SW27.1, SW37.1, SW39.1, SW42.1, SW43.1, SW51.1, SW56.1
7: J1.5, SW1.1, SW3.1, SW5.1, SW7.1, SW9.1, SW12.1, SW57.1, SW66.1
8: J1.3, SW62.1
+5V: J1.4, R1.1
A: J1.20, SW2.2, SW3.2, SW18.2, SW39.2, SW50.2, SW60.2, SW61.2, SW65.2
B: J1.19, SW4.2, SW5.2, SW23.2, SW27.2, SW41.2, SW45.2, SW48.2, SW49.2
C: J1.18, SW6.2, SW7.2, SW25.2, SW26.2, SW28.2, SW40.2, SW42.2, SW46.2
D: J1.17, SW8.2, SW9.2, SW24.2, SW29.2, SW30.2, SW43.2, SW44.2, SW47.2
E: J1.16, SW1.2, SW10.2, SW31.2, SW32.2, SW33.2, SW35.2, SW36.2, SW37.2
F: J1.15, SW11.2, SW12.2, SW14.2, SW16.2, SW19.2, SW20.2, SW34.2, SW38.2
G: J1.14, SW13.2, SW15.2, SW17.2, SW21.2, SW22.2, SW51.2, SW66.2, SW73.2
H: J1.13, SW54.2, SW55.2, SW56.2, SW57.2, SW64.2, SW67.2, SW69.2, SW70.2
I: D1.1 (K), J1.1, SW62.2
unnamed: D1.2 (A), R1.2

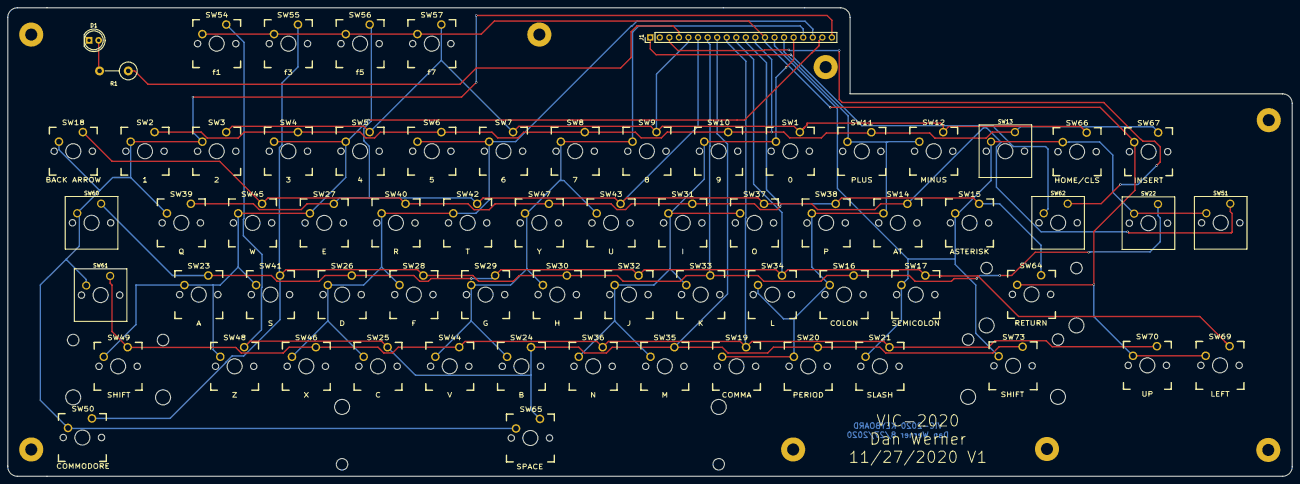
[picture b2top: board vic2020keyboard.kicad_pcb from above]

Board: 2 copper layers, 341.2 x 124.5 mm, 76 parts (0 on the bottom side), 20 nets.

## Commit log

2020-12-12 Initial docs
2020-12-13 Change Boot message in ROM
2020-12-13 Case Changes . . . enlarge case for proper cartridge fit
2020-12-13 Case Changes . . . add LED opening
2020-12-15 add contact info into the readme
2020-12-15 Case Changes . . . final tweaks
2020-12-24 modify cartridge opening
2020-12-25 Add Keyboard Spacer
2021-01-04 added case pictures
2021-04-03 Correct SVIDEO connector footprint
2021-04-03 Add Svideo comment in Readme
2021-07-03 update docs
2021-07-04 readme changes
2021-08-04 update PCB
2021-08-16 Update README/SVIDEO STILL BROKEN
2021-08-16 Fix SVIDEO (again)
2022-10-17 doc updates
